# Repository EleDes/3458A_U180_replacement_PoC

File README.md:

# x180
PoC functional replacement of the U180 hybrid for the HPAK 3458A A3 ADC.

REV C: redesign with low stray capacitance & back to discrete resistors

-- untested --

The different revisions are in the corresponding branches ( main -> dropdown )

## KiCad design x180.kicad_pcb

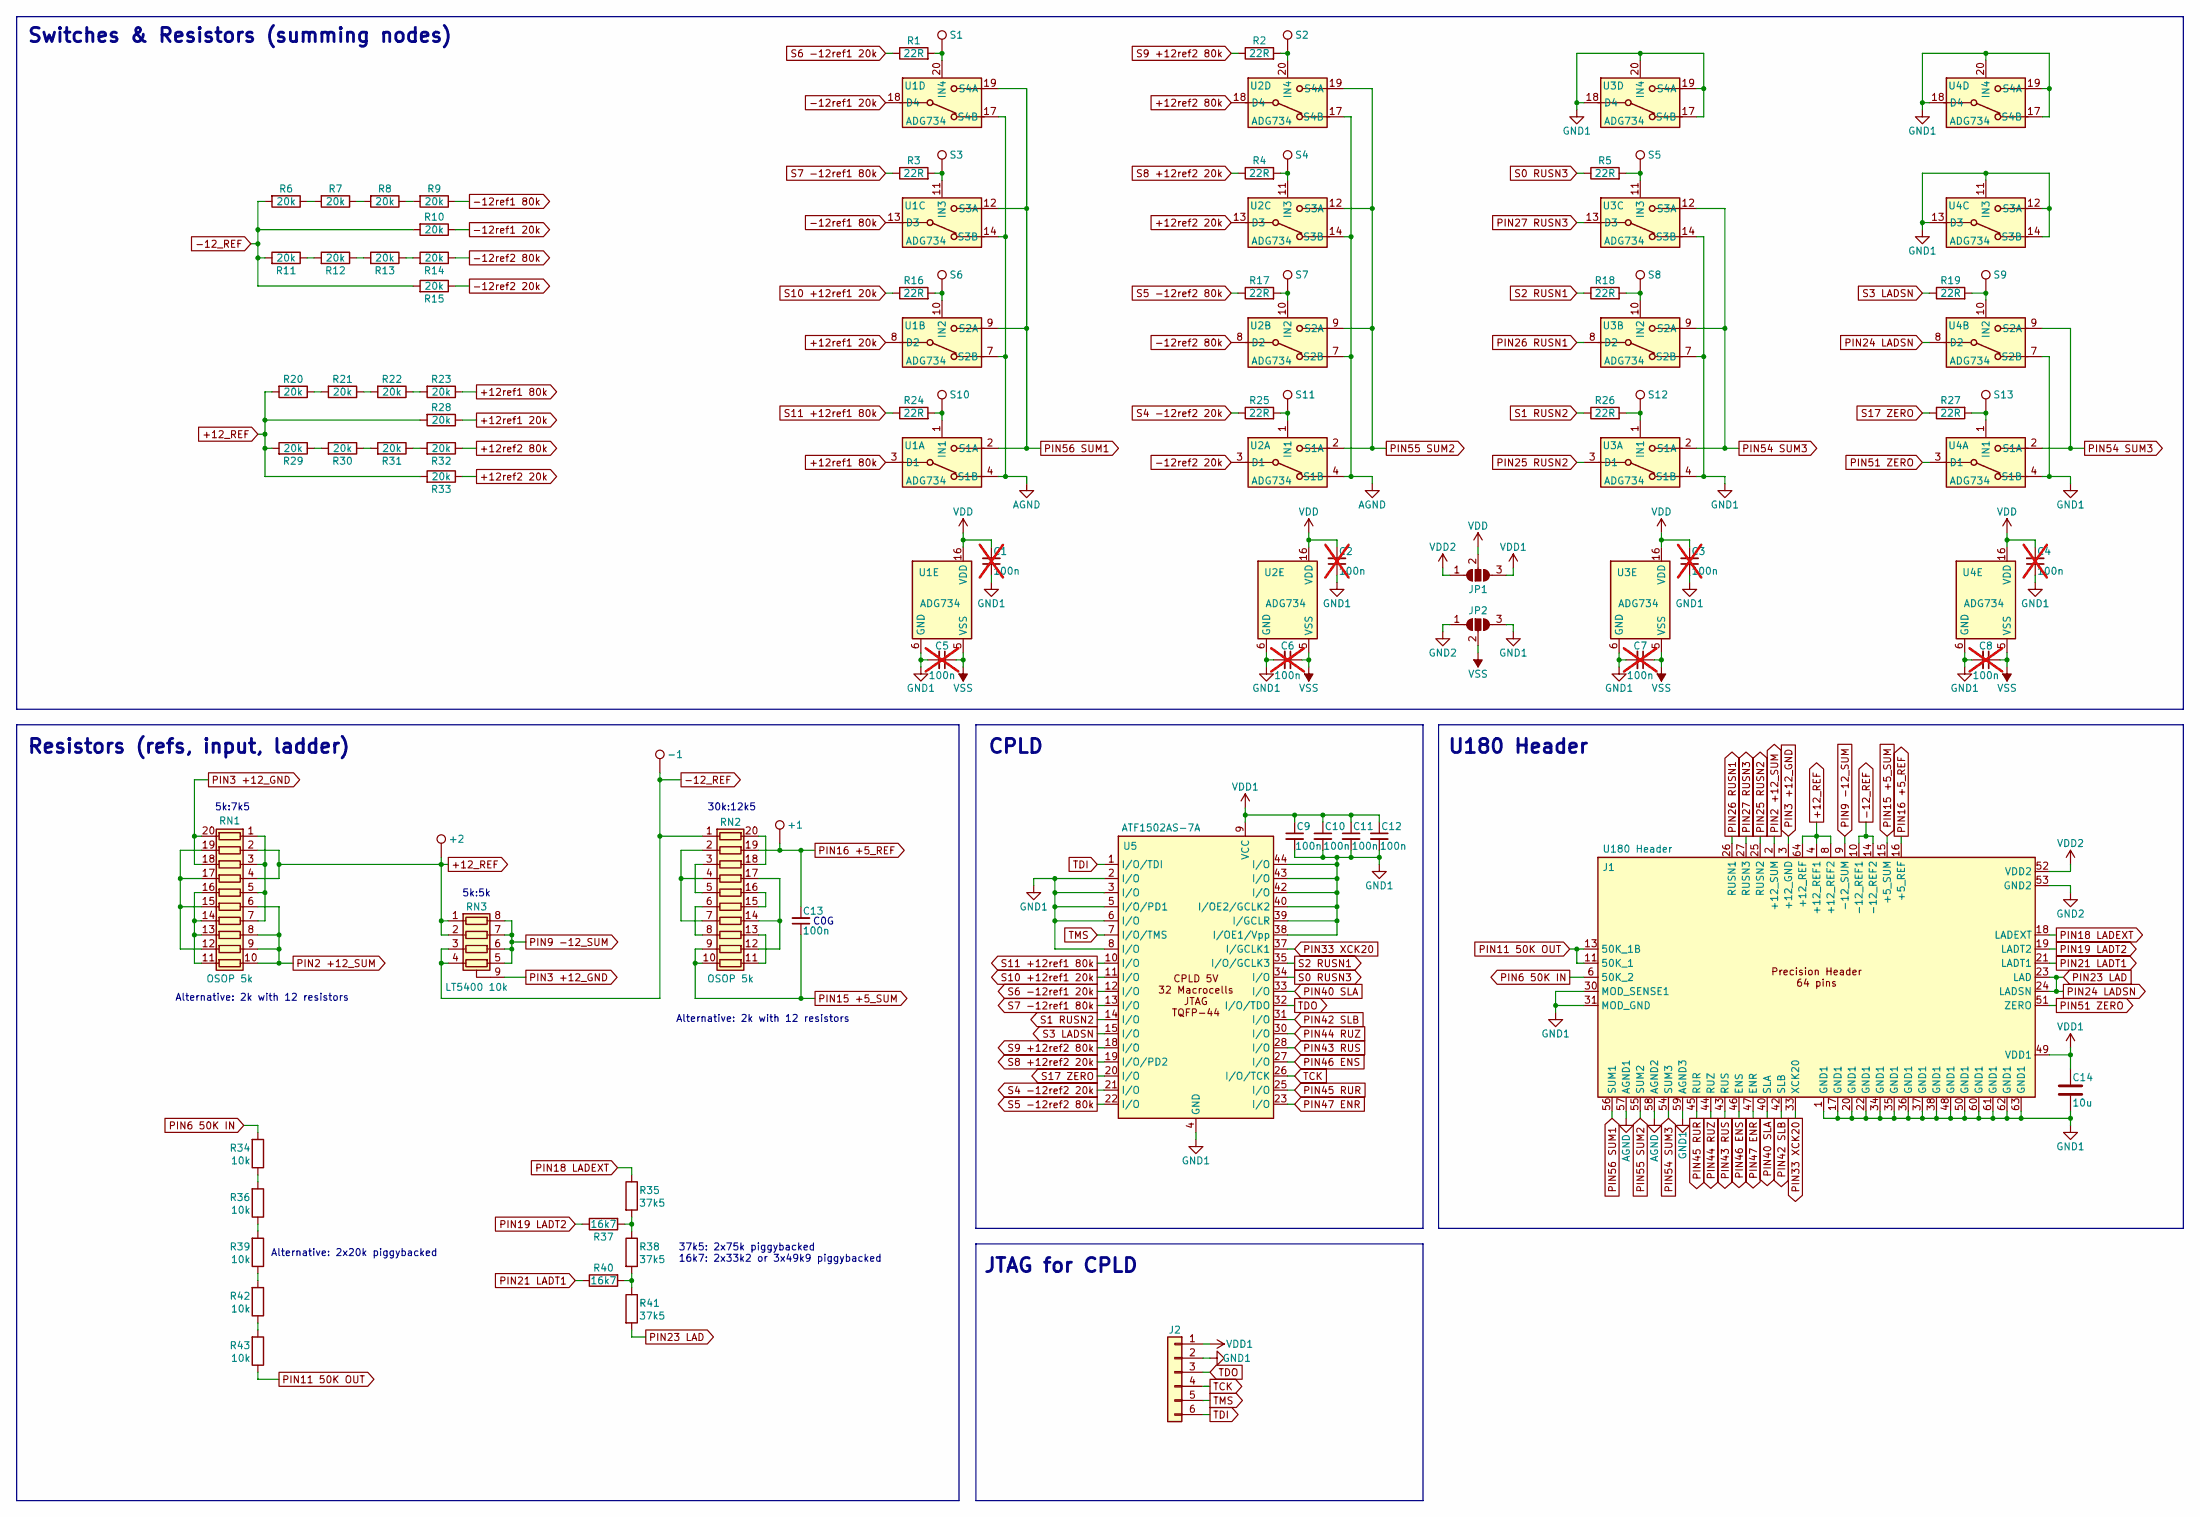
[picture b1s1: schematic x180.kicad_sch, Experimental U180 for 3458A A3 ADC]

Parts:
+1, +2: TestPoint_Small; TestPoint_Pad_D1.0mm
-1: TestPoint_Small; TestPoint_Pad_D1.0mm
C1, C2, C3, C4, C5, C6, C7, C8: 100n; C_0603_1608Metric; not fitted
C9, C10, C11, C12: 100n; C_0603_1608Metric
C13: 100n; C_1206_3216Metric
C14: 10u; C_1206_3216Metric
J1: U180 Header; U180_HEADER_64P
J2: Conn_01x06_Pin; PinHeader_1x06_P2.54mm_Vertical
JP1, JP2: SolderJumper_3_Open; SolderJumper-3_P0.7mm_Open_RoundedPad0.7x0.4mm
R1, R2, R3, R4, R5, R16, R17, R18, R19, R24, R25, R26, R27: 22R; R_0603_1608Metric
R6, R7, R8, R9, R10, R11, R12, R13, R14, R15, R20, R21, R22, R23, R28, R29, R30, R31, R32, R33: 20k; R_1206_3216Metric
R34, R36, R39, R42, R43: 10k; R_1206_3216Metric
R35, R38, R41: 37k5; R_0805_2012Metric
R37, R40: 16k7; R_0805_2012Metric
RN1, RN2: OSOP 5k; SSOP-20_3.9x8.7mm_P0.635mm
RN3: LT5400 10k; MSOP-8-1EP_3x3mm_P0.65mm_EP1.68x1.88mm
S1, S2, S3, S4, S5, S6, S7, S8, S9, S10, S11, S12, S13: TestPoint_Small; TestPoint_Pad_D1.0mm
U1, U2, U3, U4: ADG734; TSSOP-20_4.4x6.5mm_P0.65mm
U5: ATF1502AS-7A; TQFP-44_10x10mm_P0.8mm

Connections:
+12_REF: +2.1, J1.4 (+12_REF1), J1.8 (+12_REF2), J1.64 (+12_REF), R20.2, R28.2, R29.2, R33.2, RN1.2 (R2.1), RN1.4 (R4.1), RN3.1 (R1.1), RN3.2 (R2.1); also elsewhere on the board
+12ref1 20k: R28.1, U1.8 (D2)
+12ref1 80k: R23.1, U1.3 (D1)
+12ref2 20k: R33.1, U2.13 (D3)
+12ref2 80k: R32.1, U2.18 (D4)
-12_REF: -1.1, J1.10 (-12_REF1), J1.14 (-12_REF2), R6.2, R10.2, R11.2, R15.2, RN2.1 (R1.1), RN3.3 (R3.1), RN3.4 (R4.1); also elsewhere on the board
-12ref1 20k: R10.1, U1.18 (D4)
-12ref1 80k: R9.1, U1.13 (D3)
-12ref2 20k: R15.1, U2.3 (D1)
-12ref2 80k: R14.1, U2.8 (D2)
AGND: J1.57 (AGND1), J1.58 (AGND2), U1.4 (S1B), U1.7 (S2B), U1.14 (S3B), U1.17 (S4B), U2.4 (S1B), U2.7 (S2B), U2.14 (S3B), U2.17 (S4B)
GND1: C1.1, C2.1, C3.1, C4.1, C5.2, C6.2, C7.2, C8.2, C9.2, C10.2, C11.2, C12.2, C14.1, J1.1 (GND1), J1.17 (GND1), J1.20 (GND1), J1.22 (GND1), J1.30 (MOD_SENSE1), J1.31 (MOD_GND), J1.34 (GND1), J1.35 (GND1), J1.36 (GND1), J1.37 (GND1), J1.38 (GND1), J1.48 (GND1), J1.50 (GND1), J1.59 (AGND3), J1.60 (GND1), J1.61 (GND1), J1.62 (GND1), J1.63 (GND1), J2.2, JP2.3 (B), U1.6 (GND), U2.6 (GND), U3.4 (S1B), U3.6 (GND), U3.7 (S2B), U3.14 (S3B), U3.17 (S4B), U3.18 (D4), U3.19 (S4A), U3.20 (IN4), U4.4 (S1B), U4.6 (GND), U4.7 (S2B), U4.11 (IN3), U4.12 (S3A), U4.13 (D3), U4.14 (S3B), U4.17 (S4B), U4.18 (D4), U4.19 (S4A), U4.20 (IN4), U5.2 (I/O), U5.3 (I/O), U5.4 (GND), U5.5 (I/O/PD1), U5.6 (I/O), U5.8 (I/O), U5.16 (GND), U5.24 (GND), U5.36 (GND), U5.38 (I/OE1/Vpp), U5.39 (I/GCLR), U5.40 (I/OE2/GCLK2), U5.42 (I/O), U5.43 (I/O), U5.44 (I/O)
GND2: J1.53 (GND2), JP2.1 (A)
unnamed: R6.1, R7.2
unnamed: R7.1, R8.2
unnamed: R8.1, R9.2
unnamed: R11.1, R12.2
unnamed: R12.1, R13.2
unnamed: R13.1, R14.2
unnamed: R20.1, R21.2
unnamed: R21.1, R22.2
unnamed: R22.1, R23.2
unnamed: R29.1, R30.2
unnamed: R30.1, R31.2
unnamed: R31.1, R32.2
unnamed: R34.1, R36.2
unnamed: R35.2, R37.2, R38.1
unnamed: R36.1, R39.2
unnamed: R38.2, R40.2, R41.1
unnamed: R39.1, R42.2
unnamed: R42.1, R43.2
unnamed: RN1.1 (R1.1), RN1.3 (R3.1), RN1.5 (R5.1), RN1.7 (R7.1)
unnamed: RN1.12 (R9.2), RN1.15 (R6.2), RN1.17 (R4.2), RN1.19 (R2.2)
unnamed: RN1.11 (R10.2), RN1.13 (R8.2), RN1.14 (R7.2), RN1.16 (R5.2)
unnamed: RN2.18 (R3.2), RN2.20 (R1.2)
unnamed: RN2.2 (R2.1), RN2.4 (R4.1), RN2.7 (R7.1)
unnamed: RN2.3 (R3.1), RN2.5 (R5.1)
unnamed: RN2.12 (R9.2), RN2.14 (R7.2), RN2.17 (R4.2)
unnamed: RN2.15 (R6.2), RN2.16 (R5.2)
unnamed: RN2.6 (R6.1), RN2.8 (R8.1)
unnamed: RN2.11 (R10.2), RN2.13 (R8.2)
unnamed: R24.2, S10.1, U1.1 (IN1)
unnamed: R16.2, S6.1, U1.10 (IN2)
unnamed: R3.2, S3.1, U1.11 (IN3)
unnamed: R1.2, S1.1, U1.20 (IN4)
unnamed: R25.2, S11.1, U2.1 (IN1)
unnamed: R17.2, S7.1, U2.10 (IN2)
unnamed: R4.2, S4.1, U2.11 (IN3)
unnamed: R2.2, S2.1, U2.20 (IN4)
unnamed: R26.2, S12.1, U3.1 (IN1)
unnamed: R18.2, S8.1, U3.10 (IN2)
unnamed: R5.2, S5.1, U3.11 (IN3)
unnamed: R27.2, S13.1, U4.1 (IN1)
unnamed: R19.2, S9.1, U4.10 (IN2)
PIN2 +12_SUM: J1.2 (+12_SUM), RN1.6 (R6.1), RN1.8 (R8.1), RN1.9 (R9.1), RN1.10 (R10.1)
PIN3 +12_GND: J1.3 (+12_GND), RN1.18 (R3.2), RN1.20 (R1.2), RN3.9 (R1.2)
PIN6 50K IN: J1.6 (50K_2), R34.2
PIN9 -12_SUM: J1.9 (-12_SUM), RN3.5 (R4.2), RN3.6 (R3.2), RN3.7 (R2.2), RN3.8 (R1.2)
PIN11 50K OUT: J1.11 (50K_1), J1.13 (50K_1B), R43.1
PIN15 +5_SUM: C13.1, J1.15 (+5_SUM), RN2.9 (R9.1), RN2.10 (R10.1)
PIN16 +5_REF: +1.1, C13.2, J1.16 (+5_REF), RN2.19 (R2.2); also elsewhere on the board
PIN18 LADEXT: J1.18 (LADEXT), R35.1
PIN19 LADT2: J1.19 (LADT2), R37.1
PIN21 LADT1: J1.21 (LADT1), R40.1
PIN23 LAD: J1.23 (LAD), J1.24 (LADSN), R41.2, U4.8 (D2)
PIN25 RUSN2: J1.25 (RUSN2), U3.3 (D1)
PIN26 RUSN1: J1.26 (RUSN1), U3.8 (D2)
PIN27 RUSN3: J1.27 (RUSN3), U3.13 (D3)
PIN33 XCK20: J1.33 (XCK20), U5.37 (I/GCLK1)
PIN40 SLA: J1.40 (SLA), U5.33 (I/O)
PIN42 SLB: J1.42 (SLB), U5.31 (I/O)
PIN43 RUS: J1.43 (RUS), U5.28 (I/O)
PIN44 RUZ: J1.44 (RUZ), U5.30 (I/O)
PIN45 RUR: J1.45 (RUR), U5.25 (I/O)
PIN46 ENS: J1.46 (ENS), U5.27 (I/O)
PIN47 ENR: J1.47 (ENR), U5.23 (I/O)
PIN51 ZERO: J1.51 (ZERO), U4.3 (D1)
PIN54 SUM3: J1.54 (SUM3), U3.2 (S1A), U3.9 (S2A), U3.12 (S3A), U4.2 (S1A), U4.9 (S2A)
PIN55 SUM2: J1.55 (SUM2), U2.2 (S1A), U2.9 (S2A), U2.12 (S3A), U2.19 (S4A)
PIN56 SUM1: J1.56 (SUM1), U1.2 (S1A), U1.9 (S2A), U1.12 (S3A), U1.19 (S4A)
S0 RUSN3: R5.1, U5.34 (I/O)
S1 RUSN2: R26.1, U5.14 (I/O)
S2 RUSN1: R18.1, U5.35 (I/O/GCLK3)
S3 LADSN: R19.1, U5.15 (I/O)
S4 -12ref2 20k: R25.1, U5.21 (I/O)
S5 -12ref2 80k: R17.1, U5.22 (I/O)
S6 -12ref1 20k: R1.1, U5.12 (I/O)
S7 -12ref1 80k: R3.1, U5.13 (I/O)
S8 +12ref2 20k: R4.1, U5.19 (I/O/PD2)
S9 +12ref2 80k: R2.1, U5.18 (I/O)
S10 +12ref1 20k: R16.1, U5.11 (I/O)
S11 +12ref1 80k: R24.1, U5.10 (I/O)
S17 ZERO: R27.1, U5.20 (I/O)
TCK: J2.4, U5.26 (I/O/TCK)
TDI: J2.6, U5.1 (I/O/TDI)
TDO: J2.3, U5.32 (I/O/TDO)
TMS: J2.5, U5.7 (I/O/TMS)
VDD: C1.2, C2.2, C3.2, C4.2, JP1.2 (C), U1.16 (VDD), U2.16 (VDD), U3.16 (VDD), U4.16 (VDD)
VDD1: C9.1, C10.1, C11.1, C12.1, C14.2, J1.49 (VDD1), J2.1, JP1.3 (B), U5.9 (VCC), U5.17 (VCC), U5.29 (VCC), U5.41 (VCC)
VDD2: J1.52 (VDD2), JP1.1 (A)
VSS: C5.1, C6.1, C7.1, C8.1, JP2.2 (C), U1.5 (VSS), U2.5 (VSS), U3.5 (VSS), U4.5 (VSS)

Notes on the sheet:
5k:7k5
5k:5k
Alternative: 2x20k piggybacked
Alternative: 2k with 12 resistors
JTAG for CPLD
Resistors (refs, input, ladder)
37k5: 2x75k piggybacked 16k7: 2x33k2 or 3x49k9 piggybacked
Switches & Resistors (summing nodes)
30k:12k5
C0G
U180 Header
CPLD

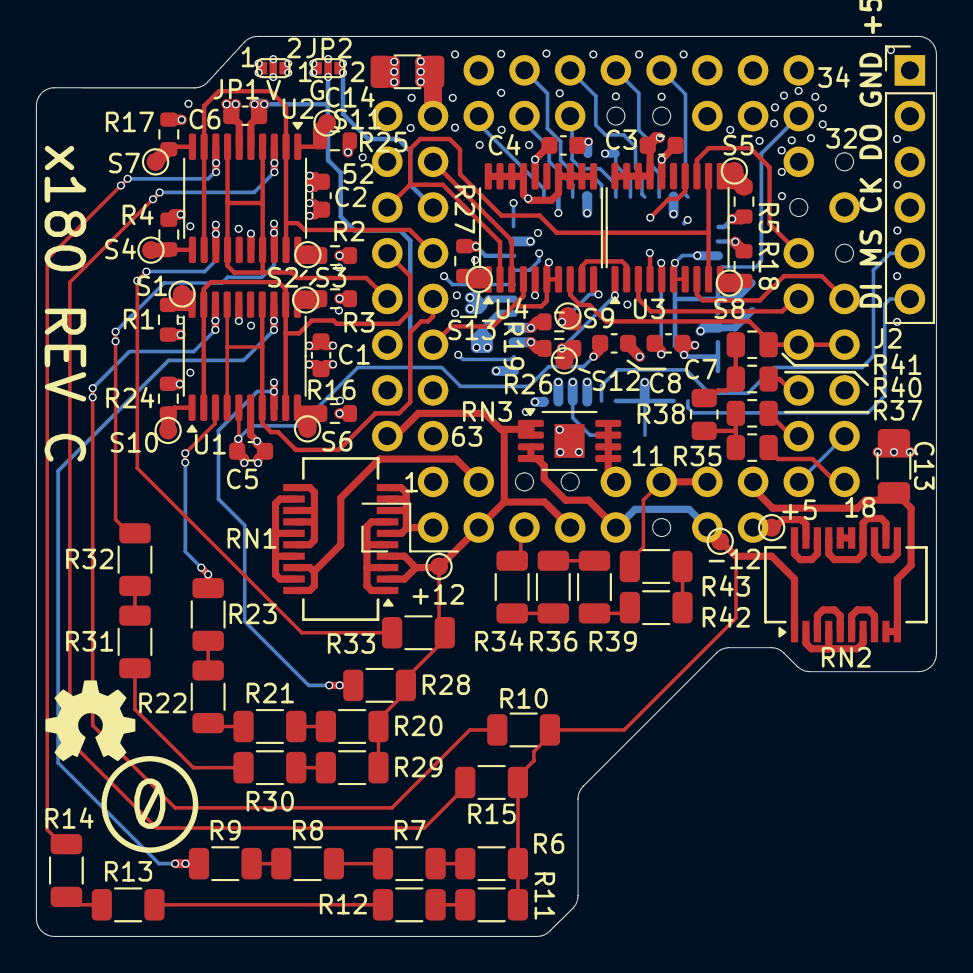
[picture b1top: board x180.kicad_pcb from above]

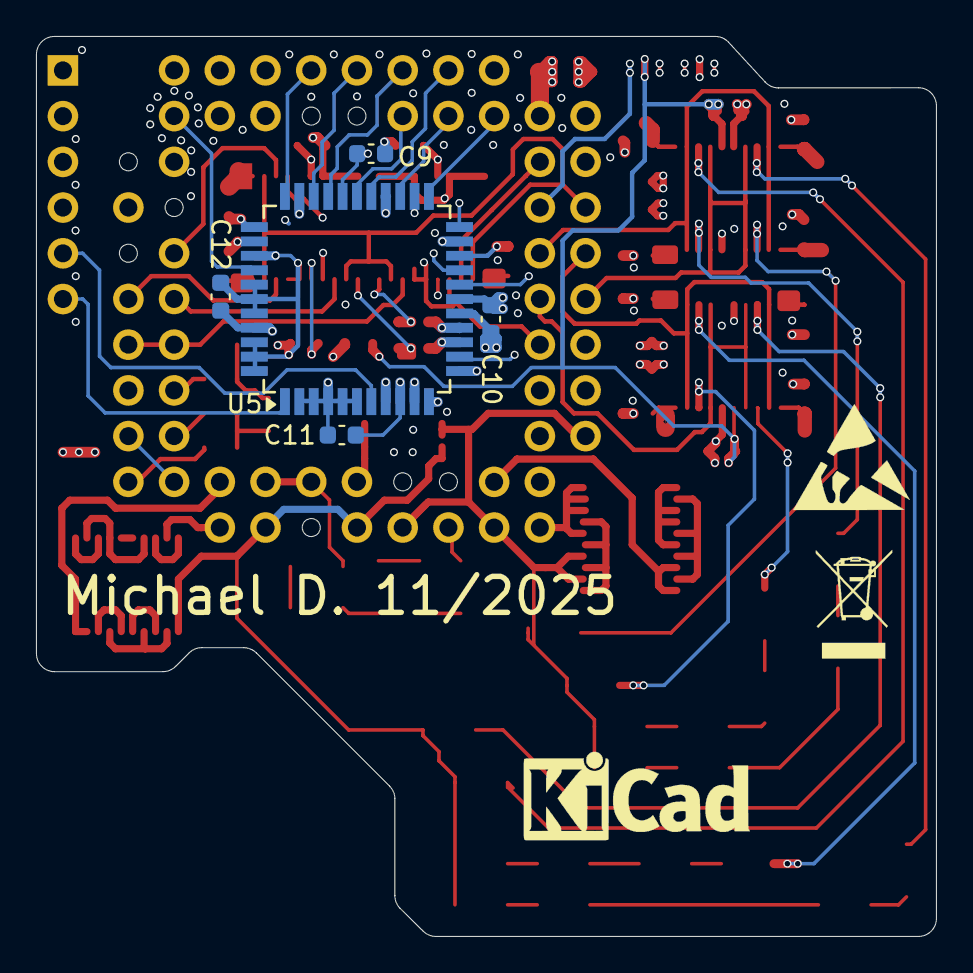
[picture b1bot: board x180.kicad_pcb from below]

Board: 6 copper layers, 50.0 x 50.0 mm, 85 parts (5 on the bottom side), 101 nets.

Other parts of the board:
+5, +12: TestPoint_Small; TestPoint_Pad_D1.0mm
-12: TestPoint_Small; TestPoint_Pad_D1.0mm

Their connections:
+12_REF: +12.1; also elsewhere on the board
-12_REF: -12.1; also elsewhere on the board
PIN16 +5_REF: +5.1; also elsewhere on the board

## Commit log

2025-09-30 Initial
2025-11-17 Minor improvements on routing
2025-11-17 CPLD files added
2025-11-19 REV B: redesign with resistor networks
2025-11-19 REV C: optimized for low stray capacitance & back to discrete resistors
